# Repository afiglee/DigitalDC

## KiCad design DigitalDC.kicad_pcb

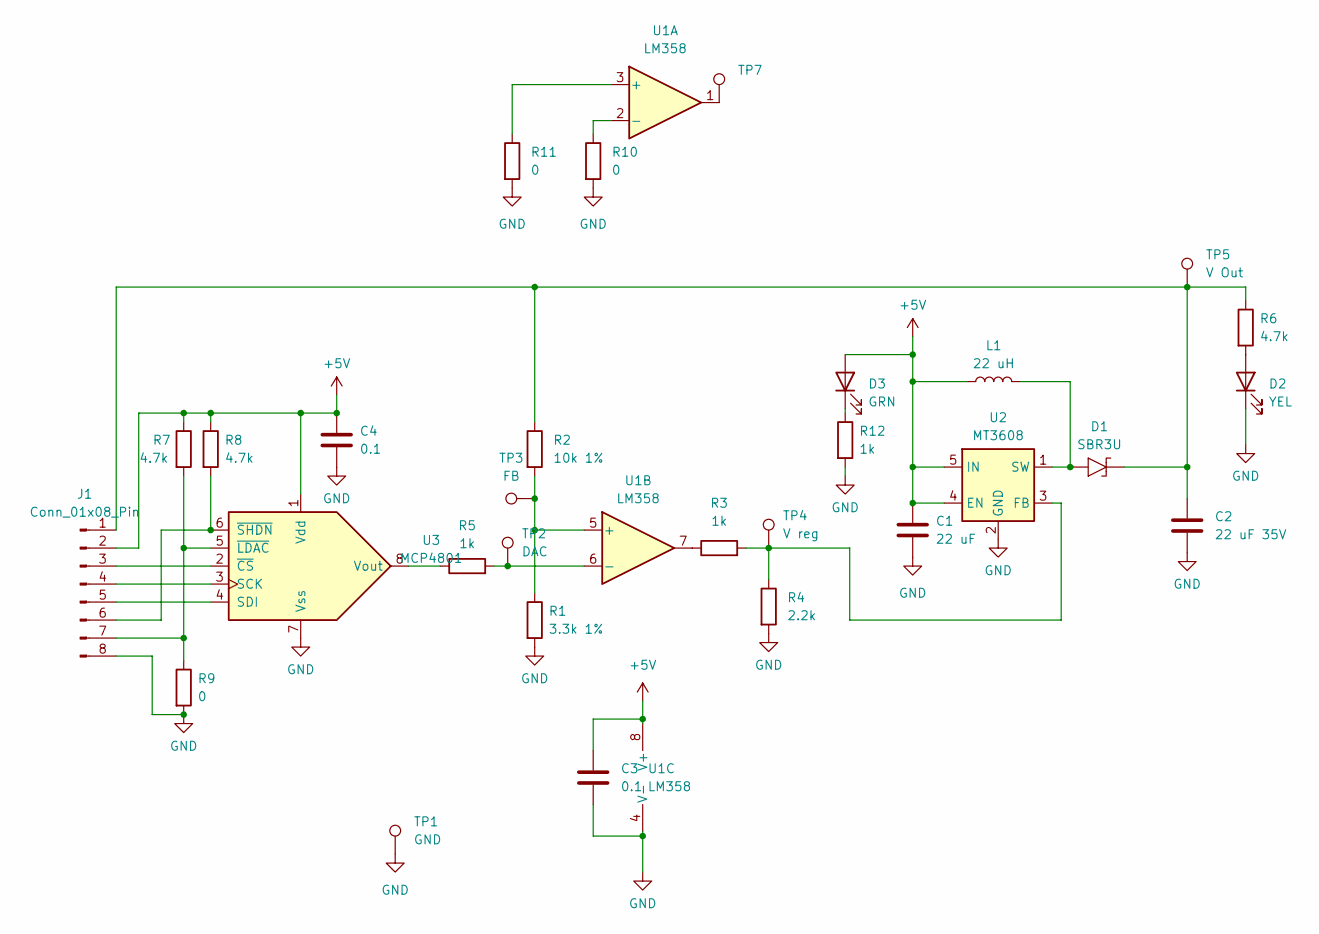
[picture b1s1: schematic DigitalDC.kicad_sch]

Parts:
C1: 22 uF; C_0603_1608Metric_Pad1.08x0.95mm_HandSolder
C2: 22 uF 35V; C_1210_3225Metric_Pad1.33x2.70mm_HandSolder
C3, C4: 0.1; C_0603_1608Metric_Pad1.08x0.95mm_HandSolder
D1: SBR3U; D_PowerDI-123
D2: YEL; LED_0805_2012Metric_Pad1.15x1.40mm_HandSolder
D3: GRN; LED_0805_2012Metric_Pad1.15x1.40mm_HandSolder
J1: Conn_01x08_Pin; PinHeader_1x08_P2.54mm_Vertical
L1: 22 uH; L_Taiyo-Yuden_NR-30xx_HandSoldering
R1: 3.3k 1%; R_0603_1608Metric_Pad0.98x0.95mm_HandSolder
R2: 10k 1%; R_0603_1608Metric_Pad0.98x0.95mm_HandSolder
R3, R5, R12: 1k; R_0603_1608Metric_Pad0.98x0.95mm_HandSolder
R4: 2.2k; R_0603_1608Metric_Pad0.98x0.95mm_HandSolder
R6, R7, R8: 4.7k; R_0603_1608Metric_Pad0.98x0.95mm_HandSolder
R9, R10, R11: 0; R_0603_1608Metric_Pad0.98x0.95mm_HandSolder
TP1: GND; TestPoint_Bridge_Pitch2.54mm_Drill1.0mm
TP2: DAC; TestPoint_Bridge_Pitch2.54mm_Drill1.0mm
TP3: FB; TestPoint_Bridge_Pitch2.54mm_Drill1.0mm
TP4: V reg; TestPoint_Bridge_Pitch2.54mm_Drill1.0mm
TP5: V Out; TestPoint_Bridge_Pitch2.54mm_Drill1.0mm
TP7: TestPoint; TestPoint_Pad_1.5x1.5mm
U1: LM358; SOIC-8_3.9x4.9mm_P1.27mm
U2: MT3608; SOT-23-6
U3: MCP4801; SOIC-8_3.9x4.9mm_P1.27mm

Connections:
+5V: C1.1, C3.1, C4.1, D3.2 (A), J1.2, L1.1, R7.1, R8.1, U1.8 (V+), U2.4 (EN), U2.5 (IN), U3.1 (Vdd)
GND: C1.2, C2.2, C3.2, C4.2, D2.1 (K), J1.8, R1.2, R4.2, R9.2, R10.2, R11.2, R12.2, TP1.1, U1.4 (V-), U2.2 (GND), U3.7 (Vss)
unnamed: D1.2 (A), L1.2, U2.1 (SW)
unnamed: C2.1, D1.1 (C), J1.1, R2.1, R6.1, TP5.1
unnamed: D2.2 (A), R6.2
unnamed: D3.1 (K), R12.1
unnamed: J1.3, U3.2 (~CS)
unnamed: J1.4, U3.3 (SCK)
unnamed: J1.5, U3.4 (SDI)
unnamed: J1.6, R8.2, U3.6 (~SHDN)
unnamed: J1.7, R7.2, R9.1, U3.5 (~LDAC)
unnamed: R3.1, U1.7
unnamed: TP7.1, U1.1
unnamed: R11.1, U1.3 (+)
unnamed: R10.1, U1.2 (-)
unnamed: R1.1, R2.2, TP3.1, U1.5 (+)
unnamed: R5.2, TP2.1, U1.6 (-)
unnamed: R3.2, R4.1, TP4.1, U2.3 (FB)
unnamed: R5.1, U3.8 (Vout)

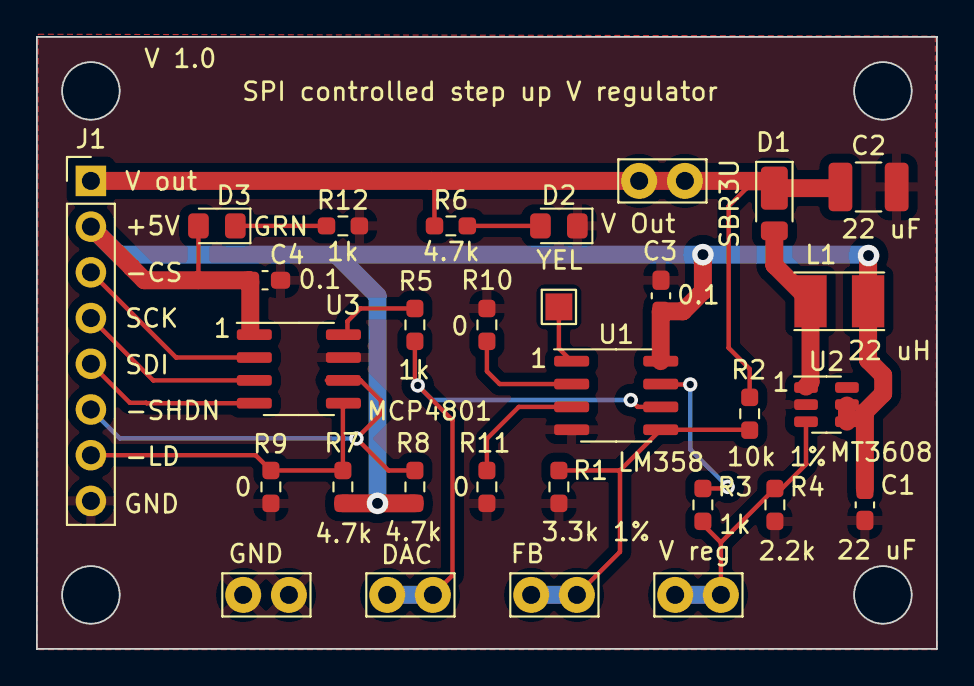
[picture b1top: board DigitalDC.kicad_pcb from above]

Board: 2 copper layers, 50.0 x 34.0 mm, 30 parts (0 on the bottom side), 19 nets.

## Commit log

2024-04-02 Initial commit, schema ready
2024-04-03 Version 1 is done
